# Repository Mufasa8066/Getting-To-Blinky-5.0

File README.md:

# Getting-To-Blinky-5.0

In this project, we are creating an blinking LED using a 7555 timer. This is a very basic and beginner board for those looking to go into the realm of PCB design.

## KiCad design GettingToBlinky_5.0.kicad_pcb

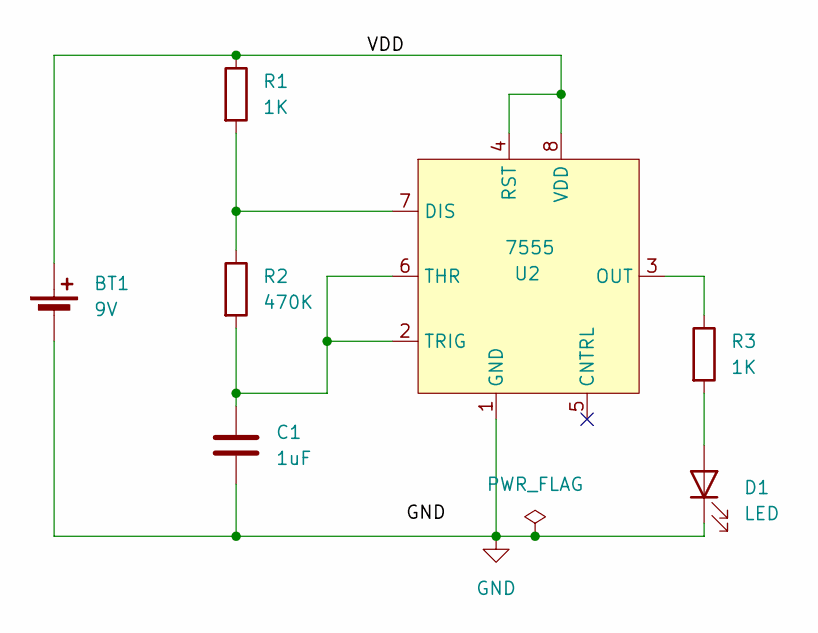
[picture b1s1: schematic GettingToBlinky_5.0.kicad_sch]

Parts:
BT1: 9V; S8211-46R
C1: 1uF; C_0805_2012Metric
D1: LED; LED_0805_2012Metric_Pad1.15x1.40mm_HandSolder
R1, R3: 1K; R_0805_2012Metric_Pad1.20x1.40mm_HandSolder
R2: 470K; R_0805_2012Metric_Pad1.20x1.40mm_HandSolder
U2: 7555; SOIC-8_3.9x4.9mm_P1.27mm

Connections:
/VDD: BT1.1 (+), R1.1, U2.4 (RST), U2.8 (VDD)
GND: BT1.2 (-), C1.2, D1.1 (K), U2.1 (GND)
unnamed: D1.2 (A), R3.2
unnamed: R1.2, R2.1, U2.7 (DIS)
unnamed: R3.1, U2.3 (OUT)
unnamed: C1.1, R2.2, U2.2 (TRIG), U2.6 (THR)

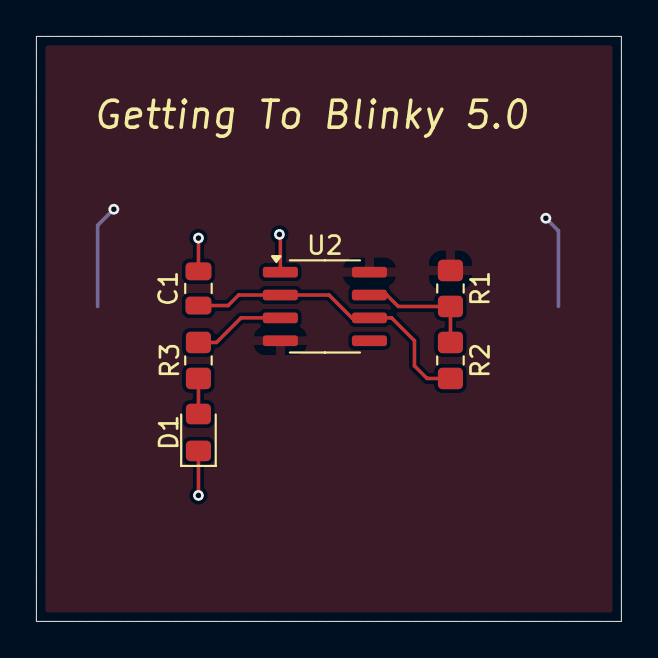
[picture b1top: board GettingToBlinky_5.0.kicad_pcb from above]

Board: 2 copper layers, 32.5 x 32.5 mm, 7 parts (1 on the bottom side), 6 nets.
